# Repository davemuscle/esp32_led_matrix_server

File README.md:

# ESP32 LED Matrix Fileserver

Upload images, gifs, and text files for display on an LED matrix!

|  |
| :--: |
| *Cat* |

The board consists of an ESP32 microcontroller and an SD card.
The SD card can be accessed remotely through a web browser, after some setup is complete.

|  |
| :--: |
| *ESP32 Board* |

## Setup Steps

### 1. Network Credentials

Remove the microSD card from the ESP32 board and insert it into a disk reader on your PC. 
Create a file called "credentials.h", or open it if it already exists.

|  |
| :--: |
| *Mounted SD card* |

Open the file in a text editor and input your network SSID and password on consecutive lines.

|  |
| :--: |
| *Credentials* |

Place the SD card back into the ESP32 board.

### 2. Power

Plug the onboard barrel-jack into a 5V DC power supply.
Anything at or above 5V-1A will work:

|  |
| :--: |
| *Example Power Supply* |

### 3. Webserver

After plugging in the board with the network credentials loaded, the ESP32 will connect to your home network.
The IP address of the ESP32 will be displayed on the LED matrix, like this:

|  |
| :--: |
| *Displayed IP* |

Note:
If the IP address is displayed is shifted and blurry, reapply power to the board or press the reset button.

|  |
| :--: |
| *Screen malfunction, reset!* |

In your web broswer, enter the IP address, eg:
```
http://192.168.86.135
```

You may be able to connect using mDNS, instead of the IP address: 
```
esp32.local
```

If that doesn't work, you need install an mDNS service like Bonjour (Windows)

### 4. Upload Images

If the previous steps worked, you'll be able to access the fileserver:

|  |
| :--: |
| *File Server* |

The images/gifs you upload must be 64x64 in size, and text files will wrap around as needed.
The accepted file formats are:
* .txt
* .bmp
* .gif

|  |
| :--: |
| *Telepathy* |

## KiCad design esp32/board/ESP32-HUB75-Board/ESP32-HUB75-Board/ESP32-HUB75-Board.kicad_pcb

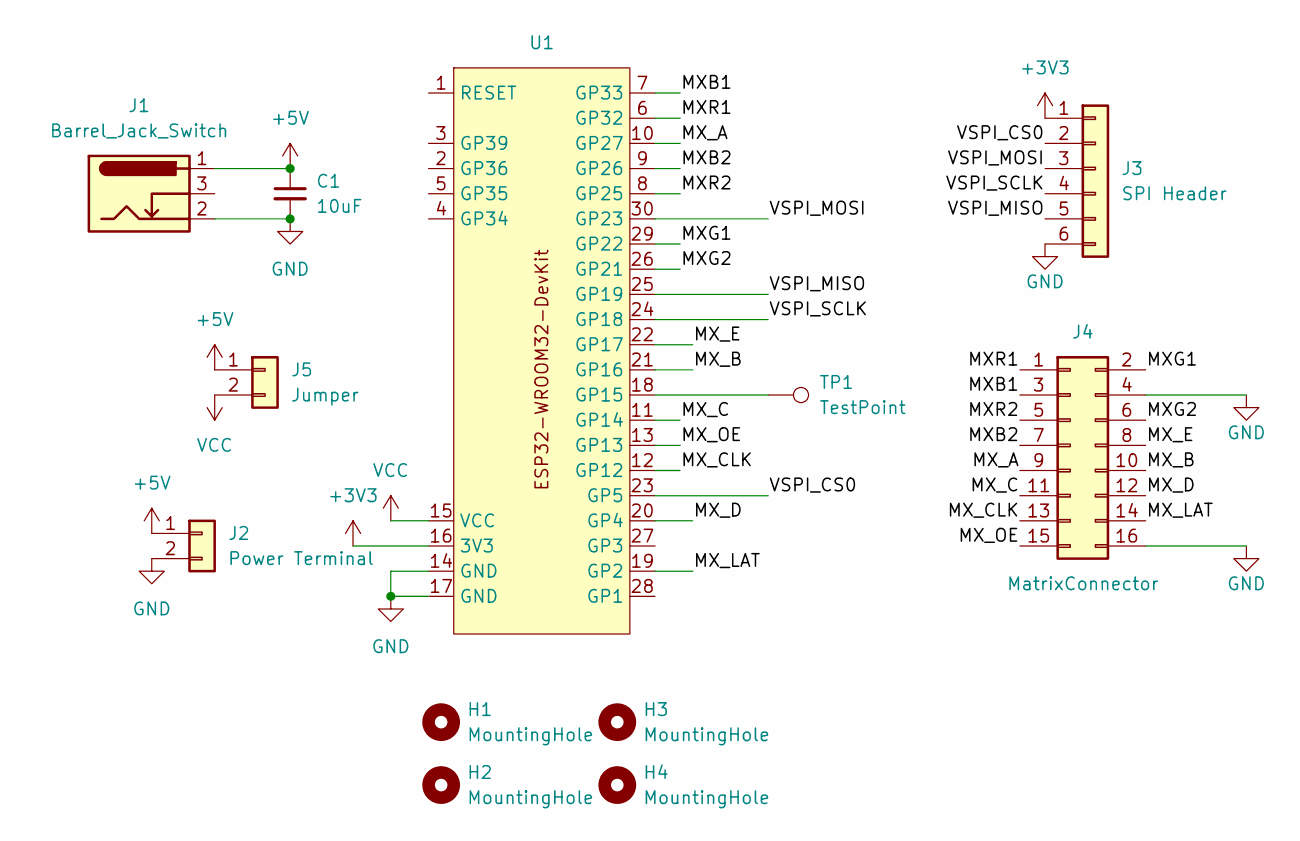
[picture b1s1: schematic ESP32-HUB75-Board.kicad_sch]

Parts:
C1: 10uF; CP_Radial_Tantal_D5.0mm_P2.50mm
H1, H2, H3, H4: MountingHole; MountingHole_2.2mm_M2
J1: Barrel_Jack_Switch; BarrelJack_GCT_DCJ200-10-A_Horizontal
J2: Power Terminal; TerminalBlock_bornier-2_P5.08mm
J3: SPI Header; PinHeader_1x06_P2.54mm_Vertical
J4: MatrixConnector; PinHeader_2x08_P2.54mm_Vertical
J5: Jumper; PinHeader_1x02_P2.54mm_Vertical
TP1: TestPoint; PinHeader_1x01_P2.54mm_Vertical
U1: ESP32-WROOM32-DevKit

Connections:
+3V3: J3.1, U1.16 (3V3)
+5V: C1.1, J1.1, J2.1, J5.1
/MXB1: J4.3, U1.7 (GP33)
/MXB2: J4.7, U1.9 (GP26)
/MXG1: J4.2, U1.29 (GP22)
/MXG2: J4.6, U1.26 (GP21)
/MXR1: J4.1, U1.6 (GP32)
/MXR2: J4.5, U1.8 (GP25)
/MX_A: J4.9, U1.10 (GP27)
/MX_B: J4.10, U1.21 (GP16)
/MX_C: J4.11, U1.11 (GP14)
/MX_CLK: J4.13, U1.12 (GP12)
/MX_D: J4.12, U1.20 (GP4)
/MX_E: J4.8, U1.22 (GP17)
/MX_LAT: J4.14, U1.19 (GP2)
/MX_OE: J4.15, U1.13 (GP13)
/VSPI_CS0: J3.2, U1.23 (GP5)
/VSPI_MISO: J3.5, U1.25 (GP19)
/VSPI_MOSI: J3.3, U1.30 (GP23)
/VSPI_SCLK: J3.4, U1.24 (GP18)
GND: C1.2, J1.2, J2.2, J3.6, J4.4, J4.16, U1.14 (GND), U1.17 (GND)
unnamed: TP1.1, U1.18 (GP15)
VCC: J5.2, U1.15 (VCC)

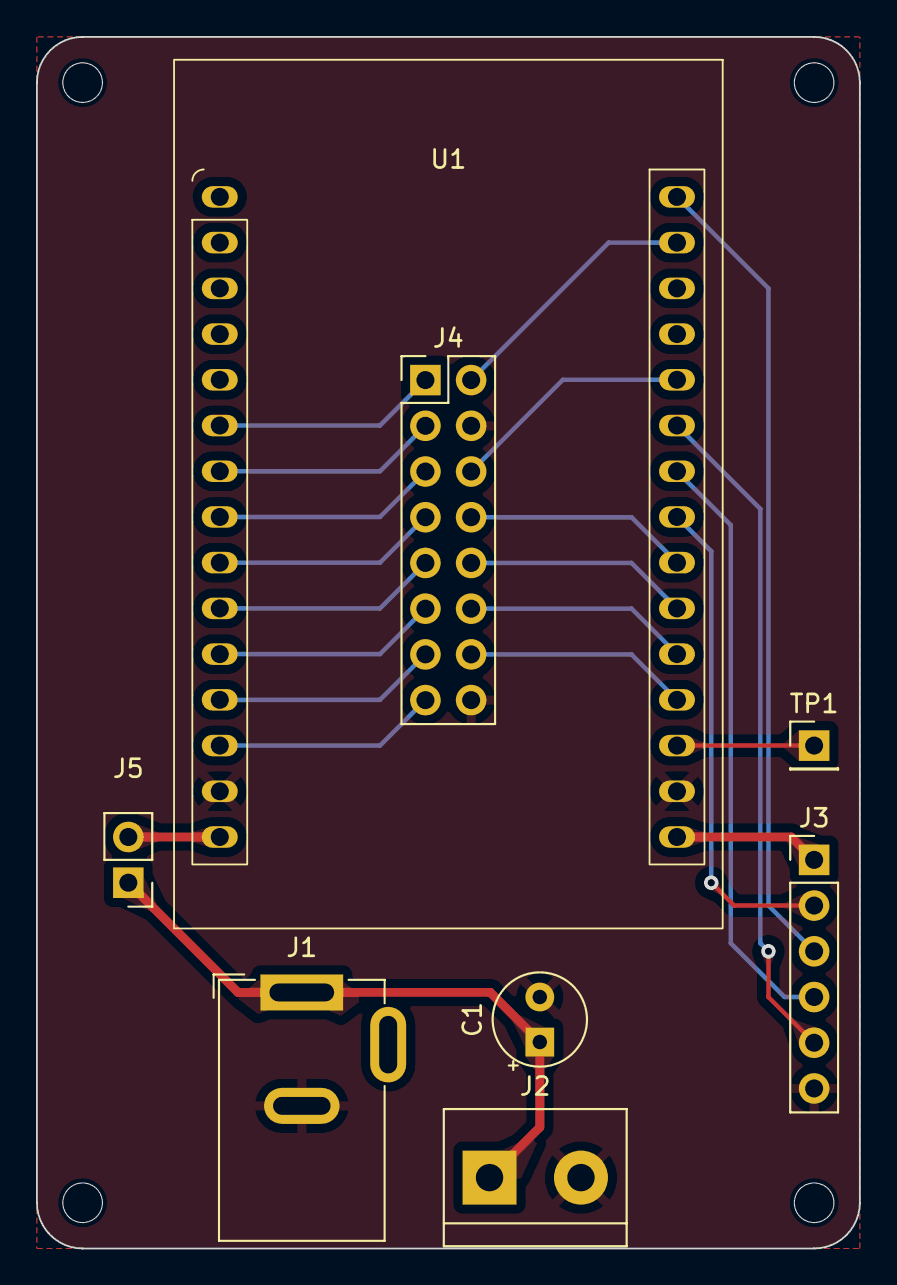
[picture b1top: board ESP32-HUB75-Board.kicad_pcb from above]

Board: 2 copper layers, 45.7 x 67.3 mm, 12 parts (0 on the bottom side), 23 nets.

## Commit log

2023-06-11 Decently working screen
2023-06-12 Added test image display. Doesn't look good though
2023-06-12 Make BCM better, change output drive
2023-07-09 Baseline ESP32
2023-07-09 Add fuse to makefile
2023-07-22 Polish
2023-07-22 Cleanup
2023-07-22 Doc fix
